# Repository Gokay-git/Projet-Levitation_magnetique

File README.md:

# Lévitation magnétique 2 axes — ENSEA

Un objet aimanté lévite au-dessus d'un plateau. Sa position latérale (X, Y), naturellement
instable, est mesurée par 3 capteurs à effet Hall et stabilisée en temps réel par 4 bobines
pilotées par une carte NUCLEO-L476RG.

**Objectif phase 1 : lévitation stable d'un objet d'au moins 800 g pour le 15 décembre 2026.**

**Carte de puissance** (shield enfiché sur la Nucleo) — [vue de dessous](Docs/images/puissance_dessous.png)

**Plateau de mesure** (3 capteurs à effet Hall) — [vue de dessous](Docs/images/plateau_dessous.png)

## Contenu du dépôt

| Dossier | Contenu |
|---|---|
| [`Hardware/`](Hardware) | Les 2 cartes KiCad : puissance et plateau |
| [`Firmware/`](Firmware) | Le projet STM32CubeIDE `LM_V2` (boucle de lévitation à 5 kHz) |
| [`Outils/`](Outils) | `lm_outil.py` : lecture du log série, calcul de L, ω₀ et β, courbes |
| [`Simulation/`](Simulation) | Le firmware compilé pour PC et testé sur un modèle de la maquette |
| [`Docs/`](Docs) | Schémas en PDF, rendus des cartes |

## Versions

Les versions figées sont dans les [Releases](../../releases) :

| Version | Contenu |
|---|---|
| `firmware-v2.0` | Projet STM32CubeIDE complet (zip) et outil PC |
| `pcb-v1.9.3` | Fichiers Gerber des 2 cartes, à envoyer au fabricant |

## État au 15 novembre 2026

- **Cartes V1.9.3** : vérification DRC sans erreur, prêtes à être commandées.
- **Firmware V2** : compile sans avertissement et a été validé en simulation (modèle instable
  2 axes + L293D + ADC, résultats dans [`Simulation/`](Simulation)). Il n'a pas encore été testé
  sur la maquette.
- **Valeurs provisoires** dans `Firmware/LM_V2/Core/Inc/LM_config.h` : R et L des bobines,
  ω₀ et β de chaque axe. Elles seront mesurées avec l'outil PC une fois les cartes reçues.

## Démarrer

- **Cartes** : schémas en PDF dans `Docs/schemas`, composants à commander dans les
  `nomenclature.csv` de `Hardware/`. Pour modifier : KiCad 7 ou plus récent, ouvrir
  `Hardware/LM_puissance/LM_puissance.kicad_pro` ou `Hardware/LM_plateau/LM_plateau.kicad_pro`.
- **Firmware** : STM32CubeIDE, **File → Open Projects from File System** → `Firmware/LM_V2`,
  puis **Project → Clean** et **Ctrl+B**. Mode d'emploi détaillé : `Firmware/LM_V2/LISEZMOI.txt`.
- **Outil PC** : voir [`Outils/README.md`](Outils/README.md).
- **Simulation** : `python Simulation/simuler.py` (compilateur C nécessaire), voir
  [`Simulation/README.md`](Simulation/README.md).

## Règles de travail

- Une seule branche `main`. Pour une modification risquée, créer une branche courte
  (ex. `pcb-v2`), puis la fusionner dans `main` par une pull request et la supprimer.
- Pas de zip ni de fichiers générés dans le dépôt : les versions figées vont dans les Releases.
- Les fichiers gardent toujours le même nom (pas de numéro de version dans le nom) :
  l'historique Git conserve toutes les versions.
- Une tâche = une *Issue*, assignée à un membre de l'équipe.

## Équipe

Gökay, Dylan, Subhen, Elias — ENSEA.

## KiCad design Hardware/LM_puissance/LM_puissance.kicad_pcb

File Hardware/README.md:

# Cartes électroniques (KiCad) — version V1.9.3

| Carte | Rôle | Composants principaux |
|---|---|---|
| `LM_puissance/` | Shield enfiché sur la NUCLEO-L476RG (CN7 / CN10) : commande des 4 bobines et acquisition | 2 × L293D (ponts X et Y), 4 × shunt 0,1 Ω 1 W + INA240A1, filtres RC des entrées ADC, régulateur L7805, protection d'entrée (P-MOS IRF4905, TVS SMBJ15A, fusible), bornier 12 V |
| `LM_plateau/` | Plateau de mesure de position, relié à la carte de puissance par un connecteur JST-XH | 3 × capteur à effet Hall DRV5055A4 (H1, H2, H3) |

Chaque dossier contient le projet (`.kicad_pro`), le schéma (`.kicad_sch`), le routage (`.kicad_pcb`)
et la **nomenclature** (`nomenclature.csv`, affichée sous forme de tableau par GitHub).
Les schémas sont aussi en PDF, lisibles sans KiCad, dans [`Docs/schemas`](../Docs/schemas).

## Composants à commander

| Carte | Nomenclature | Pièces |
|---|---|---|
| Puissance | [`LM_puissance/nomenclature.csv`](LM_puissance/nomenclature.csv) | 71 pièces (69 composants + 2 supports DIP-16) |
| Plateau | [`LM_plateau/nomenclature.csv`](LM_plateau/nomenclature.csv) | 7 composants |

À prévoir en plus, hors cartes :
- 1 carte NUCLEO-L476RG ;
- 1 câble JST-XH 6 points entre les deux cartes, câblé 1 vers 1 (2 boîtiers XHP-6 et 12 contacts, ou câble pré-serti) ;
- 1 alimentation 12 V continue (la carte est protégée par un fusible 2 A temporisé) ;
- 8 vis M3 et entretoises (4 trous de fixation par carte) ;
- les 4 bobines et les aimants (voir le point ouvert ci-dessous).

### Carte de puissance — dessus

### Carte de puissance — dessous (vue retournée)

### Plateau — dessus et dessous (vue retournée)

## Fabrication

Les fichiers Gerber de la version V1.9.3 sont dans la Release **`pcb-v1.9.3`** du dépôt.
Pour les régénérer après une modification : dans l'éditeur de PCB, **Fichiers → Fichiers de fabrication → Gerbers**.

## Points ouverts

- Les positions de H1, H2 et H3 sur le plateau sont provisoires.
- La partie physique n'est pas encore documentée : bobines (nombre de spires, fil, R, L), aimants
  (type, dimensions), objet en lévitation. Ce sont ces grandeurs qui fixent les valeurs de
  `Firmware/LM_V2/Core/Inc/LM_config.h`.
- Les valeurs de puissance (pistes, shunts) sont dimensionnées pour le L293D : à revoir en cas de passage à un pont MOSFET.

## Historique

| Version | Changement |
|---|---|
| V1.9.3 | Sérigraphie allégée : seuls restent les repères utiles au montage. Cuivre, vernis et perçages identiques à la V1.9.2 |
| V1.9.2 | Allègement des vias de masse, DRC sans erreur |

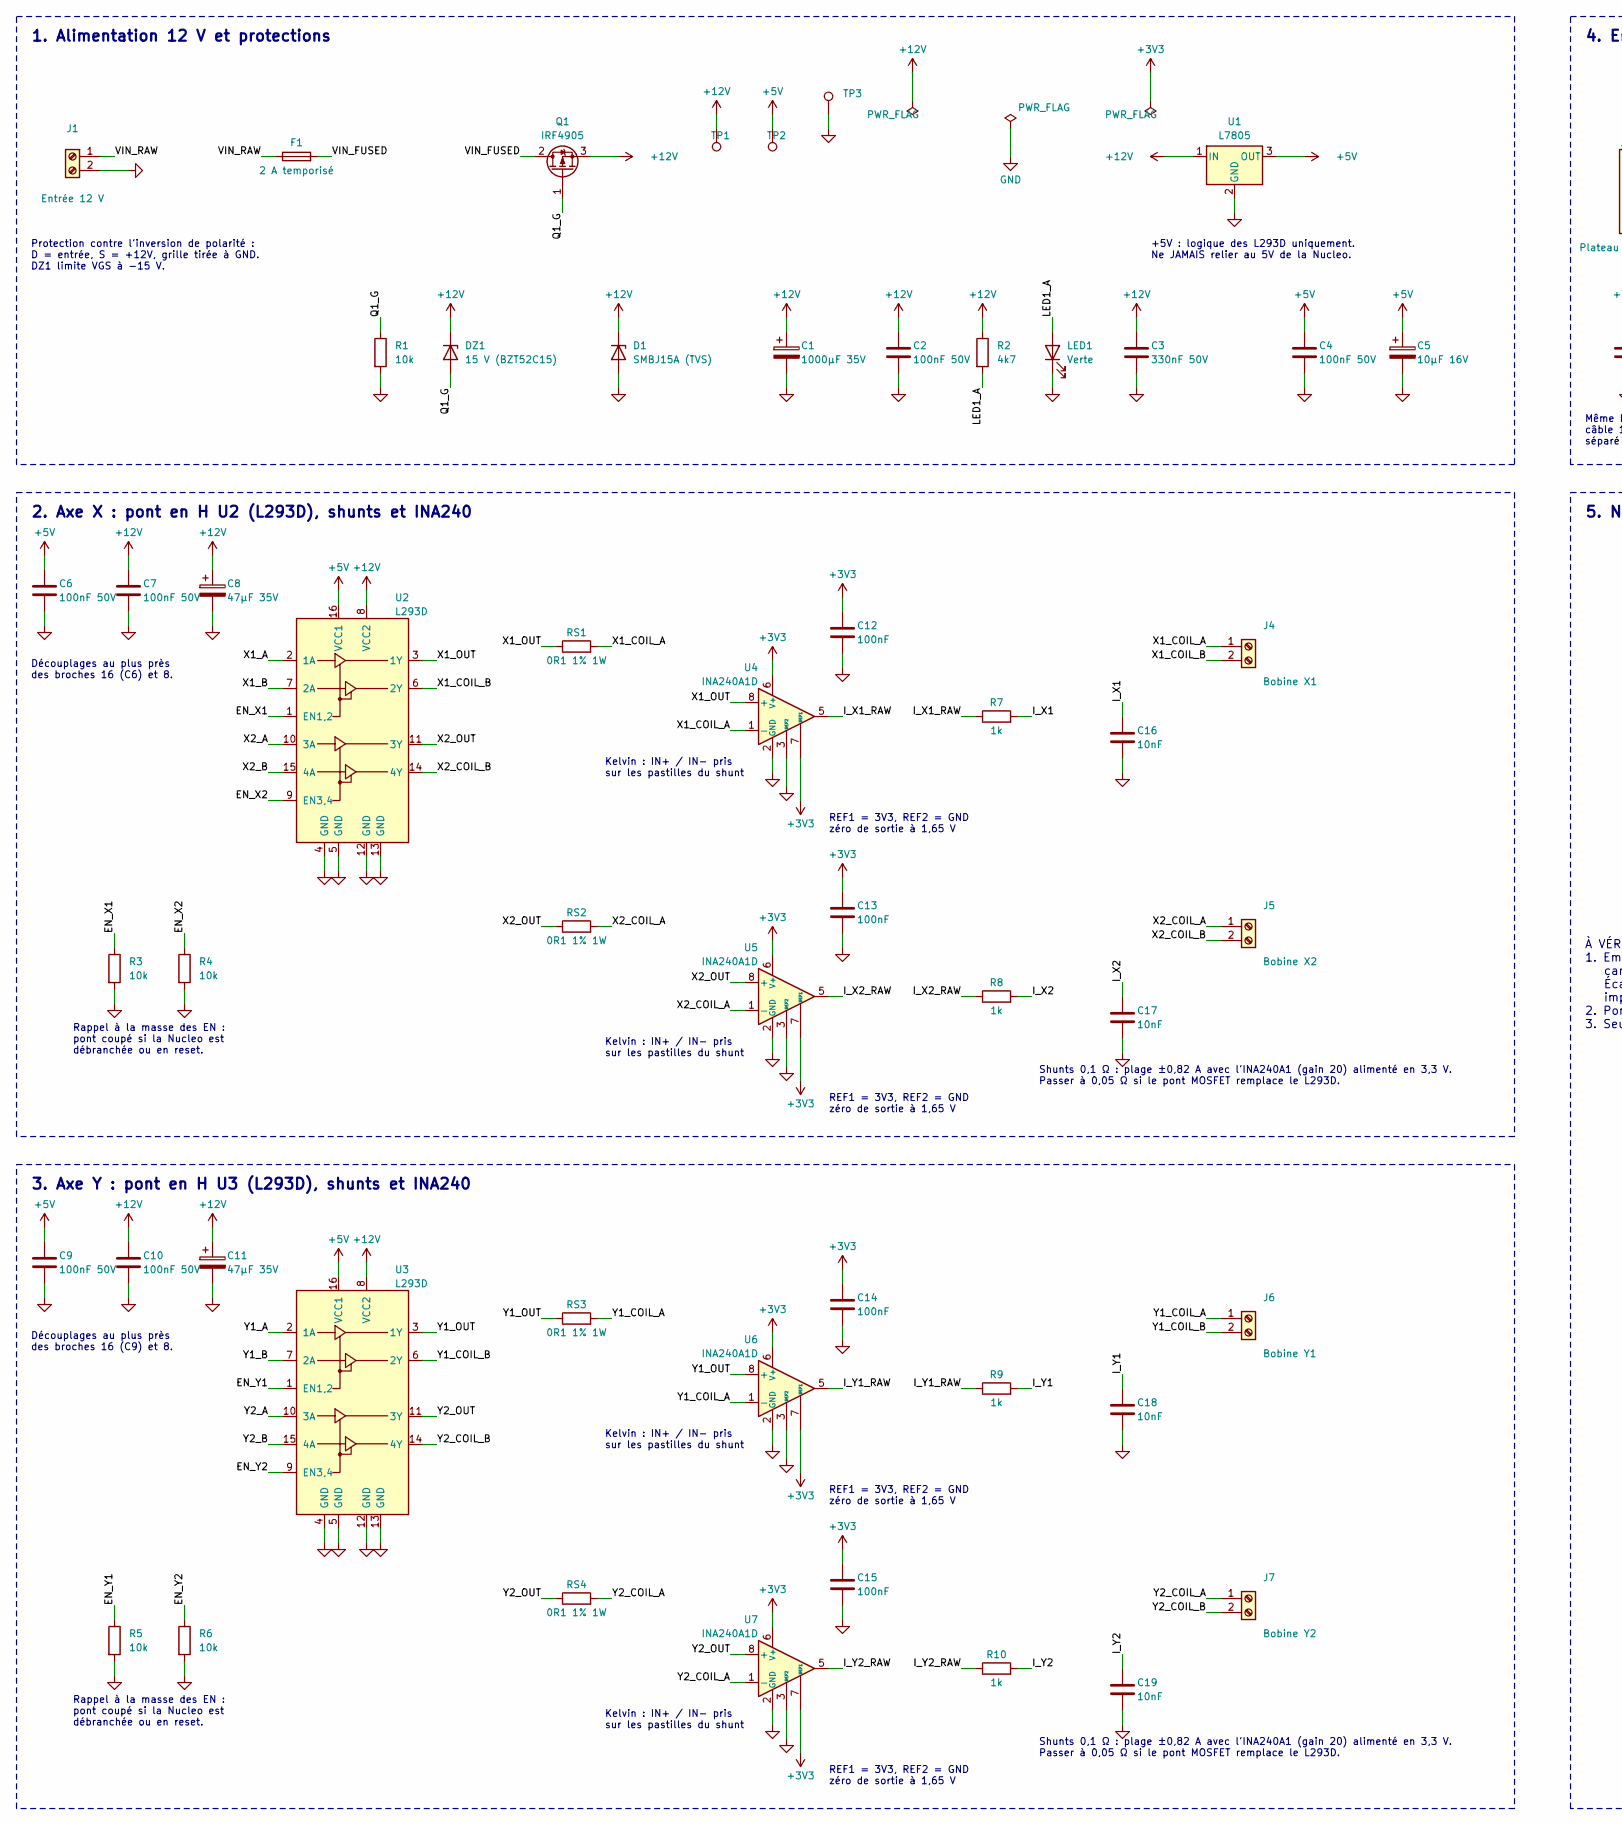
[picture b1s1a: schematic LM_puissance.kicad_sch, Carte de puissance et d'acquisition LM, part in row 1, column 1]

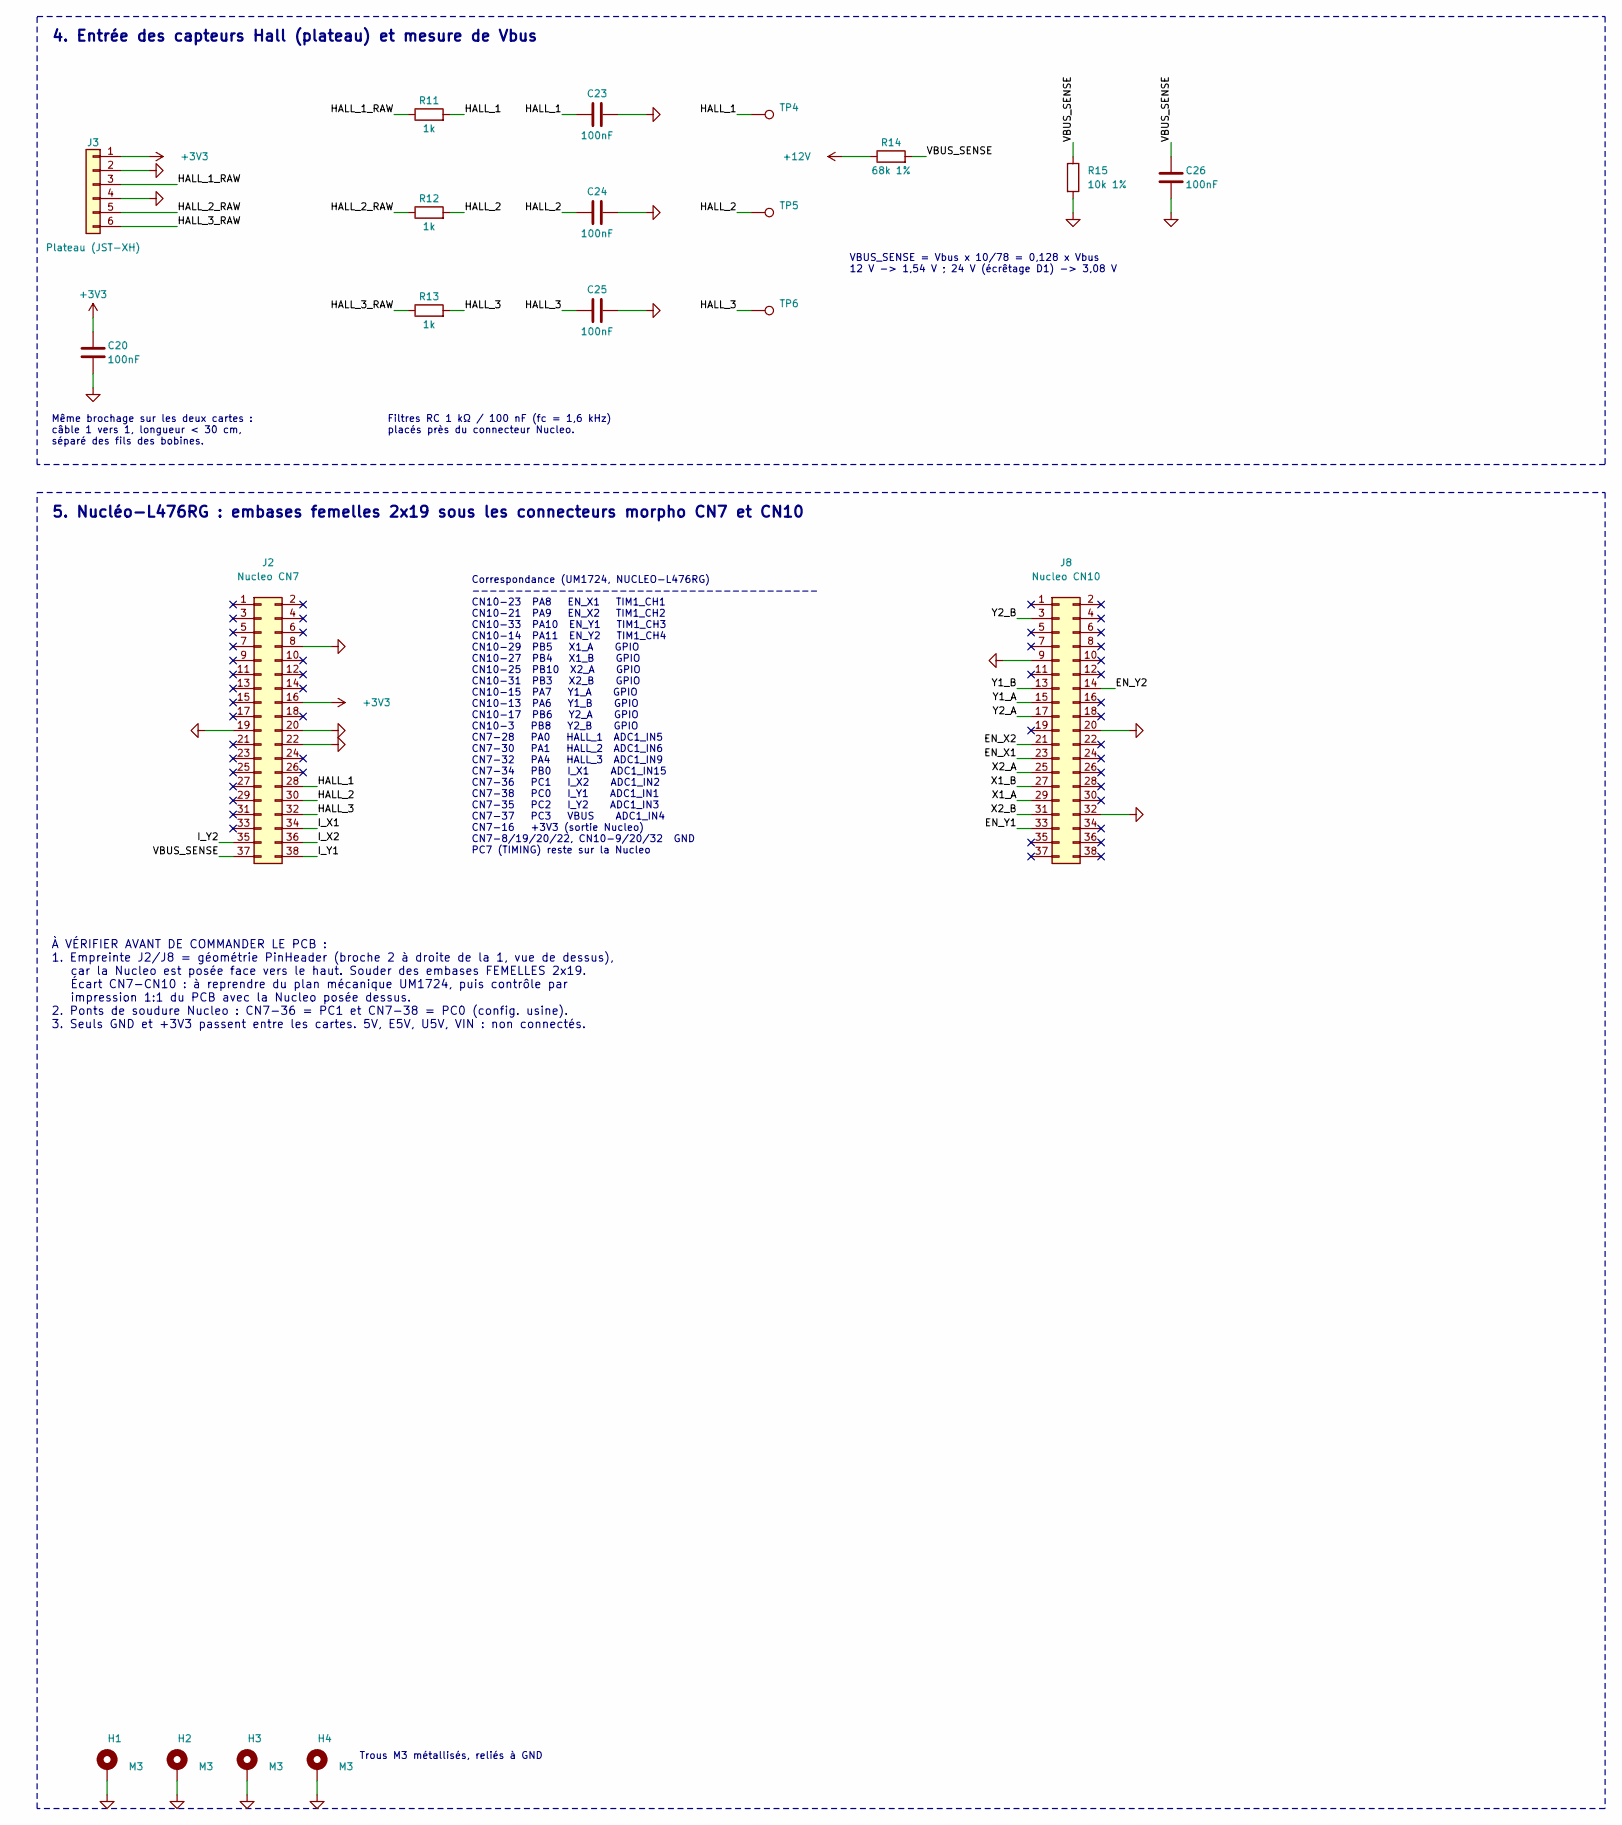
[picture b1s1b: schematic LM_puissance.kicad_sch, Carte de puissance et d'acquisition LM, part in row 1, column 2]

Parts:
C1: 1000µF 35V; CP_Radial_D10.0mm_P5.00mm
C2, C4, C6, C7, C9, C10: 100nF 50V; C_0805_2012Metric_Pad1.18x1.45mm_HandSolder
C3: 330nF 50V; C_0805_2012Metric_Pad1.18x1.45mm_HandSolder
C5: 10µF 16V; CP_Radial_D5.0mm_P2.00mm
C8, C11: 47µF 35V; CP_Radial_D6.3mm_P2.50mm
C12, C13, C14, C15, C20, C23, C24, C25, C26: 100nF; C_0805_2012Metric_Pad1.18x1.45mm_HandSolder
C16, C17, C18, C19: 10nF; C_0805_2012Metric_Pad1.18x1.45mm_HandSolder
D1: SMBJ15A (TVS); D_SMB
DZ1: 15 V (BZT52C15); D_SOD-123
F1: 2 A temporisé; Fuseholder_Cylinder-5x20mm_Schurter_0031_8201_Horizontal_Op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
H1, H2, H3, H4: M3; MountingHole_3.2mm_M3_Pad_Via
J1: Entrée 12 V; TerminalBlock_Phoenix_MKDS-1,5-2-5.08_1x02_P5.08mm_Horizont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
J2: Nucleo CN7; PinHeader_2x19_P2.54mm_Vertical
J3: Plateau (JST-XH); JST_XH_S6B-XH-A_1x06_P2.50mm_Horizontal
J4: Bobine X1; TerminalBlock_Phoenix_MKDS-1,5-2-5.08_1x02_P5.08mm_Horizont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
J5: Bobine X2; TerminalBlock_Phoenix_MKDS-1,5-2-5.08_1x02_P5.08mm_Horizont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
J6: Bobine Y1; TerminalBlock_Phoenix_MKDS-1,5-2-5.08_1x02_P5.08mm_Horizont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
J7: Bobine Y2; TerminalBlock_Phoenix_MKDS-1,5-2-5.08_1x02_P5.08mm_Horizont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
J8: Nucleo CN10; PinHeader_2x19_P2.54mm_Vertical
LED1: Verte; LED_0805_2012Metric_Pad1.15x1.40mm_HandSolder
Q1: IRF4905; TO-220-3_Vertical
R1, R3, R4, R5, R6: 10k; R_0805_2012Metric_Pad1.20x1.40mm_HandSolder
R2: 4k7; R_0805_2012Metric_Pad1.20x1.40mm_HandSolder
R7, R8, R9, R10, R11, R12, R13: 1k; R_0805_2012Metric_Pad1.20x1.40mm_HandSolder
R14: 68k 1%; R_0805_2012Metric_Pad1.20x1.40mm_HandSolder
R15: 10k 1%; R_0805_2012Metric_Pad1.20x1.40mm_HandSolder
RS1, RS2, RS3, RS4: 0R1 1% 1W; R_2512_6332Metric
TP1: +12V; TestPoint_Loop_D2.50mm_Drill1.0mm
TP2: +5V; TestPoint_Loop_D2.50mm_Drill1.0mm
TP3: GND; TestPoint_Loop_D2.50mm_Drill1.0mm
TP4: HALL_1; TestPoint_Loop_D2.50mm_Drill1.0mm
TP5: HALL_2; TestPoint_Loop_D2.50mm_Drill1.0mm
TP6: HALL_3; TestPoint_Loop_D2.50mm_Drill1.0mm
U1: L7805; TO-220-3_Vertical
U2, U3: L293D; DIP-16_W7.62mm_Socket
U4, U5, U6, U7: INA240A1D; SOIC-8_3.9x4.9mm_P1.27mm

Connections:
+3V3: C12.1, C13.1, C14.1, C15.1, C20.1, J2.16, J3.1, U4.6 (V+), U4.7 (REF1), U5.6 (V+), U5.7 (REF1), U6.6 (V+), U6.7 (REF1), U7.6 (V+), U7.7 (REF1)
+5V: C4.1, C5.1, C6.1, C9.1, TP2.1, U1.3 (OUT), U2.16 (VCC1), U3.16 (VCC1)
+12V: C1.1, C2.1, C3.1, C7.1, C8.1, C10.1, C11.1, D1.1 (K), DZ1.1 (K), Q1.3 (S), R2.1, R14.1, TP1.1, U1.1 (IN), U2.8 (VCC2), U3.8 (VCC2)
/EN_X1: J8.23, R3.1, U2.1 (EN1,2)
/EN_X2: J8.21, R4.1, U2.9 (EN3,4)
/EN_Y1: J8.33, R5.1, U3.1 (EN1,2)
/EN_Y2: J8.14, R6.1, U3.9 (EN3,4)
/HALL_1: C23.1, J2.28, R11.2, TP4.1
/HALL_1_RAW: J3.3, R11.1
/HALL_2: C24.1, J2.30, R12.2, TP5.1
/HALL_2_RAW: J3.5, R12.1
/HALL_3: C25.1, J2.32, R13.2, TP6.1
/HALL_3_RAW: J3.6, R13.1
/I_X1: C16.1, J2.34, R7.2
/I_X1_RAW: R7.1, U4.5
/I_X2: C17.1, J2.36, R8.2
/I_X2_RAW: R8.1, U5.5
/I_Y1: C18.1, J2.38, R9.2
/I_Y1_RAW: R9.1, U6.5
/I_Y2: C19.1, J2.35, R10.2
/I_Y2_RAW: R10.1, U7.5
/LED1_A: LED1.2 (A), R2.2
/Q1_G: DZ1.2 (A), Q1.1 (G), R1.1
/VBUS_SENSE: C26.1, J2.37, R14.2, R15.1
/VIN_FUSED: F1.2, Q1.2 (D)
/VIN_RAW: F1.1, J1.1
/X1_A: J8.29, U2.2 (1A)
/X1_B: J8.27, U2.7 (2A)
/X1_COIL_A: J4.1, RS1.2, U4.1 (-)
/X1_COIL_B: J4.2, U2.6 (2Y)
/X1_OUT: RS1.1, U2.3 (1Y), U4.8 (+)
/X2_A: J8.25, U2.10 (3A)
/X2_B: J8.31, U2.15 (4A)
/X2_COIL_A: J5.1, RS2.2, U5.1 (-)
/X2_COIL_B: J5.2, U2.14 (4Y)
/X2_OUT: RS2.1, U2.11 (3Y), U5.8 (+)
/Y1_A: J8.15, U3.2 (1A)
/Y1_B: J8.13, U3.7 (2A)
/Y1_COIL_A: J6.1, RS3.2, U6.1 (-)
/Y1_COIL_B: J6.2, U3.6 (2Y)
/Y1_OUT: RS3.1, U3.3 (1Y), U6.8 (+)
/Y2_A: J8.17, U3.10 (3A)
/Y2_B: J8.3, U3.15 (4A)
/Y2_COIL_A: J7.1, RS4.2, U7.1 (-)
/Y2_COIL_B: J7.2, U3.14 (4Y)
/Y2_OUT: RS4.1, U3.11 (3Y), U7.8 (+)
GND: C1.2, C2.2, C3.2, C4.2, C5.2, C6.2, C7.2, C8.2, C9.2, C10.2, C11.2, C12.2, C13.2, C14.2, C15.2, C16.2, C17.2, C18.2, C19.2, C20.2, C23.2, C24.2, C25.2, C26.2, D1.2 (A), H1.1, H2.1, H3.1, H4.1, J1.2, J2.8, J2.19, J2.20, J2.22, J3.2, J3.4, J8.9, J8.20, J8.32, LED1.1 (K), R1.2, R3.2, R4.2, R5.2, R6.2, R15.2, TP3.1, U1.2 (GND), U2.4 (GND), U2.5 (GND), U2.12 (GND), U2.13 (GND), U3.4 (GND), U3.5 (GND), U3.12 (GND), U3.13 (GND), U4.2 (GND), U4.3 (REF2), U4.4 (GND), U5.2 (GND), U5.3 (REF2), U5.4 (GND), U6.2 (GND), U6.3 (REF2), U6.4 (GND), U7.2 (GND), U7.3 (REF2), U7.4 (GND)

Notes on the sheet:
1. Alimentation 12 V et protections
Protection contre l'inversion de polarité : D = entrée, S = +12V, grille tirée à GND. DZ1 limite VGS à -15 V.
+5V : logique des L293D uniquement. Ne JAMAIS relier au 5V de la Nucleo.
2. Axe X : pont en H U2 (L293D), shunts et INA240
Rappel à la masse des EN : pont coupé si la Nucleo est débranchée ou en reset.
Découplages au plus près des broches 16 (C6) et 8.
Kelvin : IN+ / IN- pris sur les pastilles du shunt
REF1 = 3V3, REF2 = GND zéro de sortie à 1,65 V
Shunts 0,1 Ω : plage ±0,82 A avec l'INA240A1 (gain 20) alimenté en 3,3 V. Passer à 0,05 Ω si le pont MOSFET remplace le L293D.
3. Axe Y : pont en H U3 (L293D), shunts et INA240
Découplages au plus près des broches 16 (C9) et 8.
4. Entrée des capteurs Hall (plateau) et mesure de Vbus
Même brochage sur les deux cartes : câble 1 vers 1, longueur < 30 cm, séparé des fils des bobines.
Filtres RC 1 kΩ / 100 nF (fc = 1,6 kHz) placés près du connecteur Nucleo.
VBUS_SENSE = Vbus x 10/78 = 0,128 x Vbus 12 V -> 1,54 V ; 24 V (écrêtage D1) -> 3,08 V
5. Nucléo-L476RG : embases femelles 2x19 sous les connecteurs morpho CN7 et CN10
Correspondance (UM1724, NUCLEO-L476RG) ---------------------------------------- CN10-23 PA8 EN_X1 TIM1_CH1 CN10-21 PA9 EN_X2 TIM1_CH2 CN10-33 PA10 EN_Y1 TIM1_CH3 CN10-14 PA11 EN_Y2 TIM1_CH4 CN10-29 PB5 X1_A GPIO CN10-27 PB4 X1_B GPIO CN10-25 PB10 X2_A GPIO CN10-31 PB3 X2_B GPIO CN10-15 PA7 Y1_A GPI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
À VÉRIFIER AVANT DE COMMANDER LE PCB : 1. Empreinte J2/J8 = géométrie PinHeader (broche 2 à droite de la 1, vue de dessus), car la Nucleo est posée face vers le haut. Souder des embases FEMELLES 2x19. Écart CN7-CN10 : à reprendre du plan mécanique UM1724, puis contrôle par impression 1:1 du PCB ave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
Trous M3 métallisés, reliés à GND

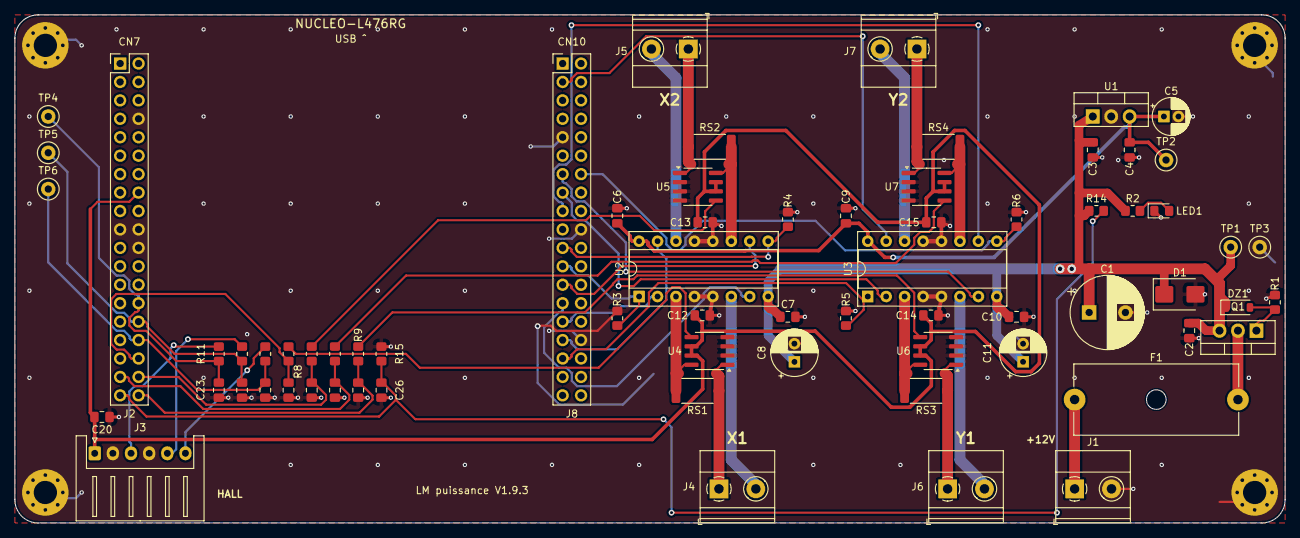
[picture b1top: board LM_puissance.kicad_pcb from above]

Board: 2 copper layers, 175.0 x 70.0 mm, 73 parts (0 on the bottom side), 47 nets.

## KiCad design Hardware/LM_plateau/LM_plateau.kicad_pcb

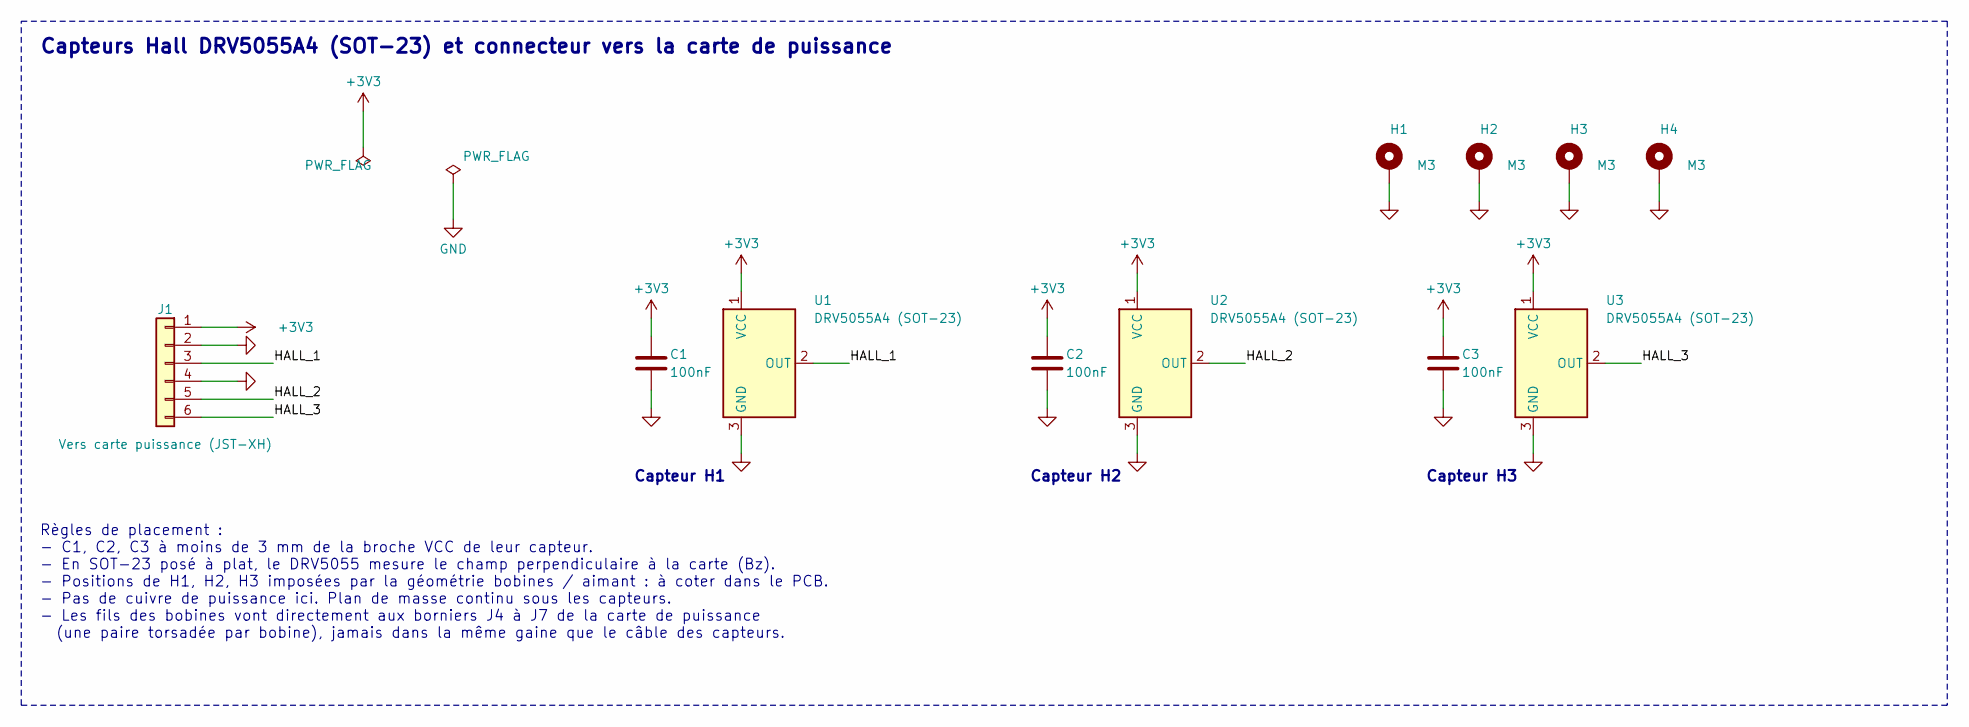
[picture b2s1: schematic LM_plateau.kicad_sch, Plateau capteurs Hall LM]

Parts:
C1, C2, C3: 100nF; C_0805_2012Metric_Pad1.18x1.45mm_HandSolder
H1, H2, H3, H4: M3; MountingHole_3.2mm_M3_Pad_Via
J1: Vers carte puissance (JST-XH); JST_XH_S6B-XH-A_1x06_P2.50mm_Horizontal
U1, U2, U3: DRV5055A4 (SOT-23); SOT-23

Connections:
+3V3: C1.1, C2.1, C3.1, J1.1, U1.1 (VCC), U2.1 (VCC), U3.1 (VCC)
/HALL_1: J1.3, U1.2 (OUT)
/HALL_2: J1.5, U2.2 (OUT)
/HALL_3: J1.6, U3.2 (OUT)
GND: C1.2, C2.2, C3.2, H1.1, H2.1, H3.1, H4.1, J1.2, J1.4, U1.3 (GND), U2.3 (GND), U3.3 (GND)

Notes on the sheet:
Capteurs Hall DRV5055A4 (SOT-23) et connecteur vers la carte de puissance
Capteur H1
Capteur H2
Capteur H3
Règles de placement : - C1, C2, C3 à moins de 3 mm de la broche VCC de leur capteur. - En SOT-23 posé à plat, le DRV5055 mesure le champ perpendiculaire à la carte (Bz). - Positions de H1, H2, H3 imposées par la géométrie bobines / aimant : à coter dans le PCB. - Pas de cuivre de puissance ici. Pla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

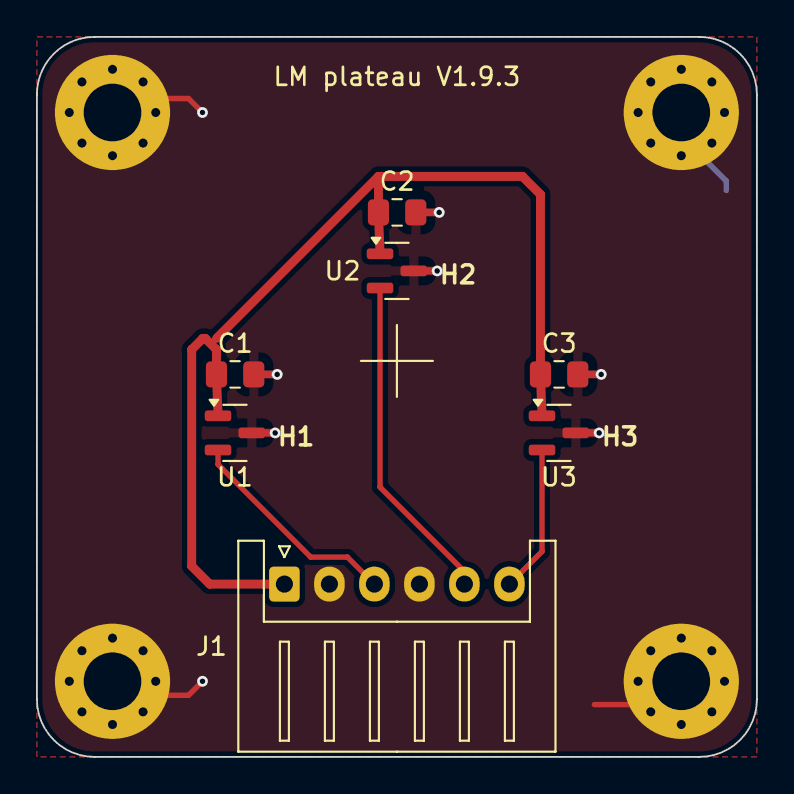
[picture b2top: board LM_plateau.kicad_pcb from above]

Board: 2 copper layers, 40.0 x 40.0 mm, 11 parts (0 on the bottom side), 5 nets.

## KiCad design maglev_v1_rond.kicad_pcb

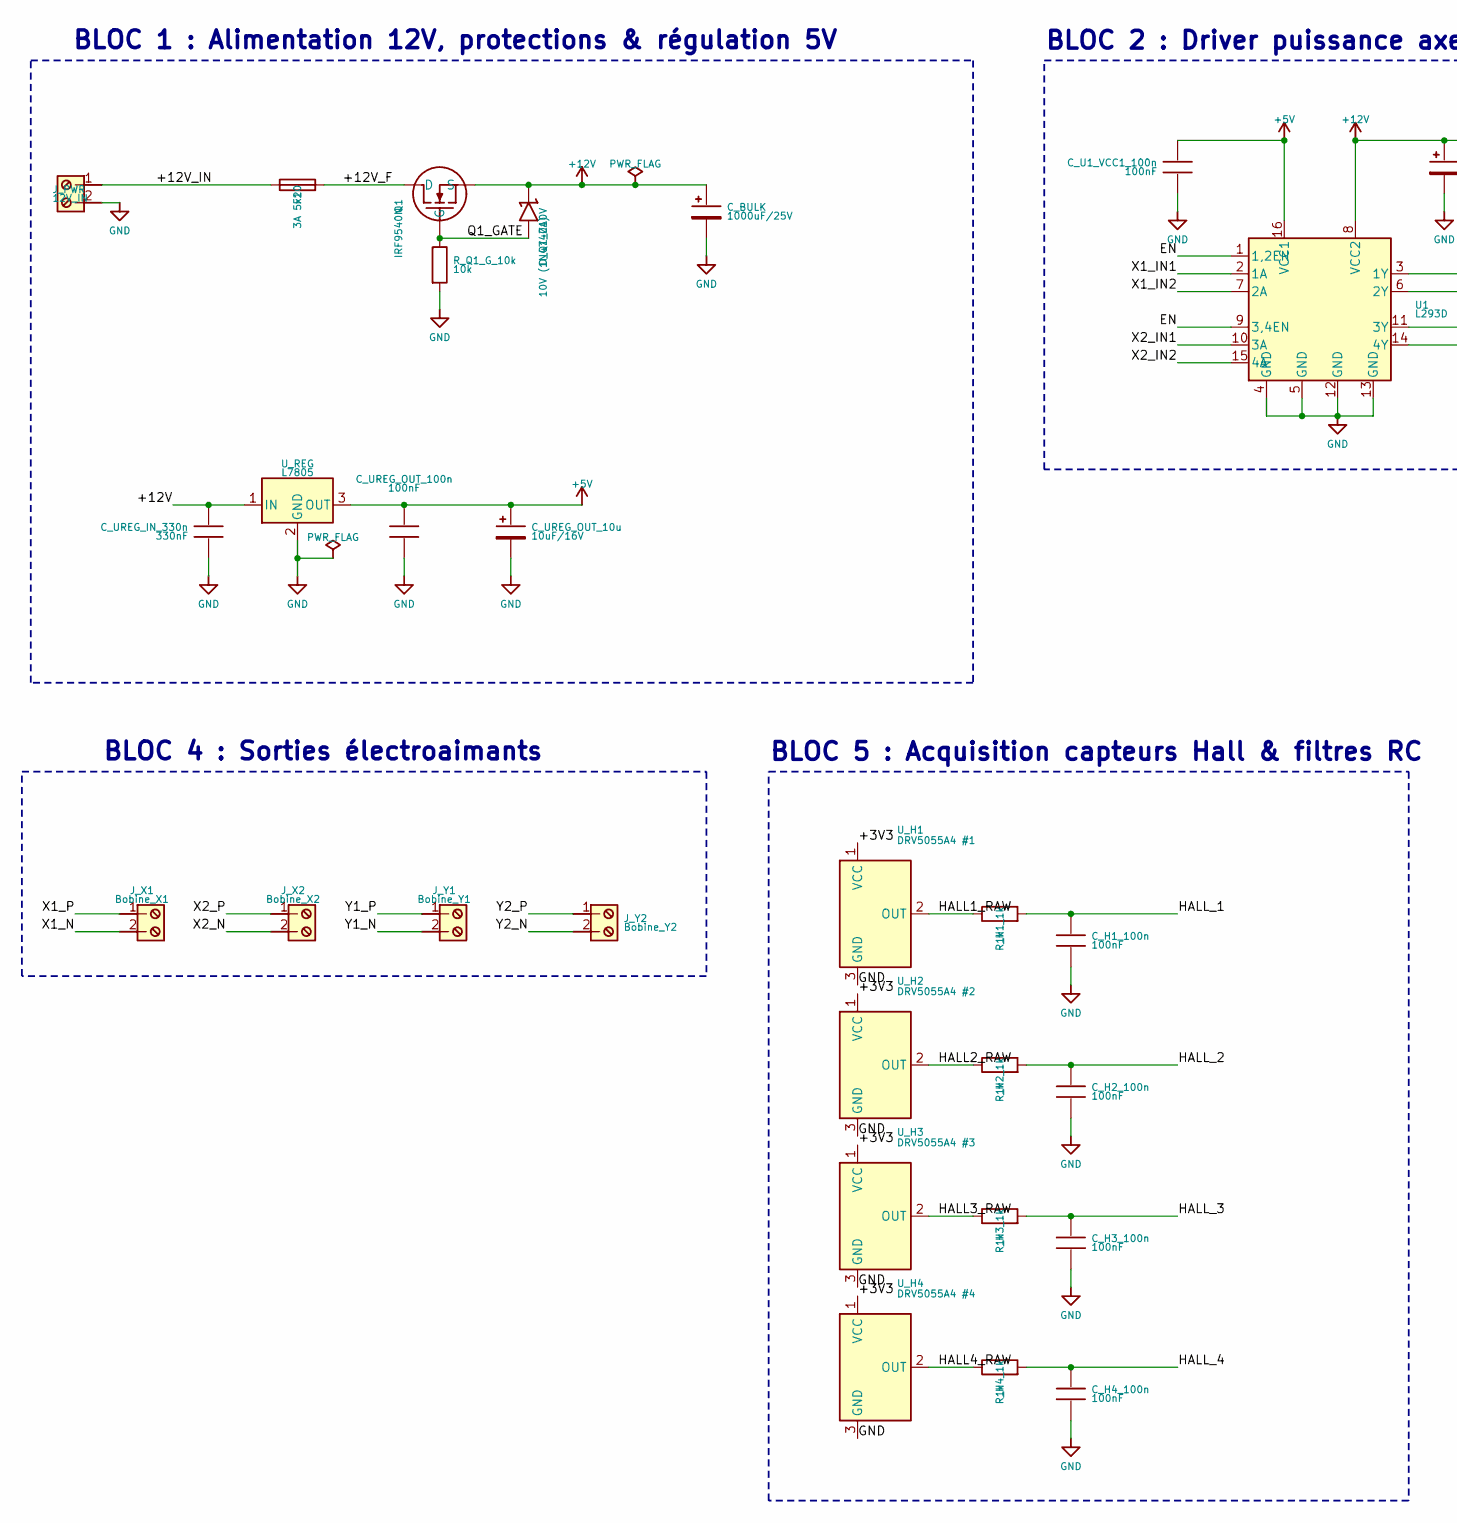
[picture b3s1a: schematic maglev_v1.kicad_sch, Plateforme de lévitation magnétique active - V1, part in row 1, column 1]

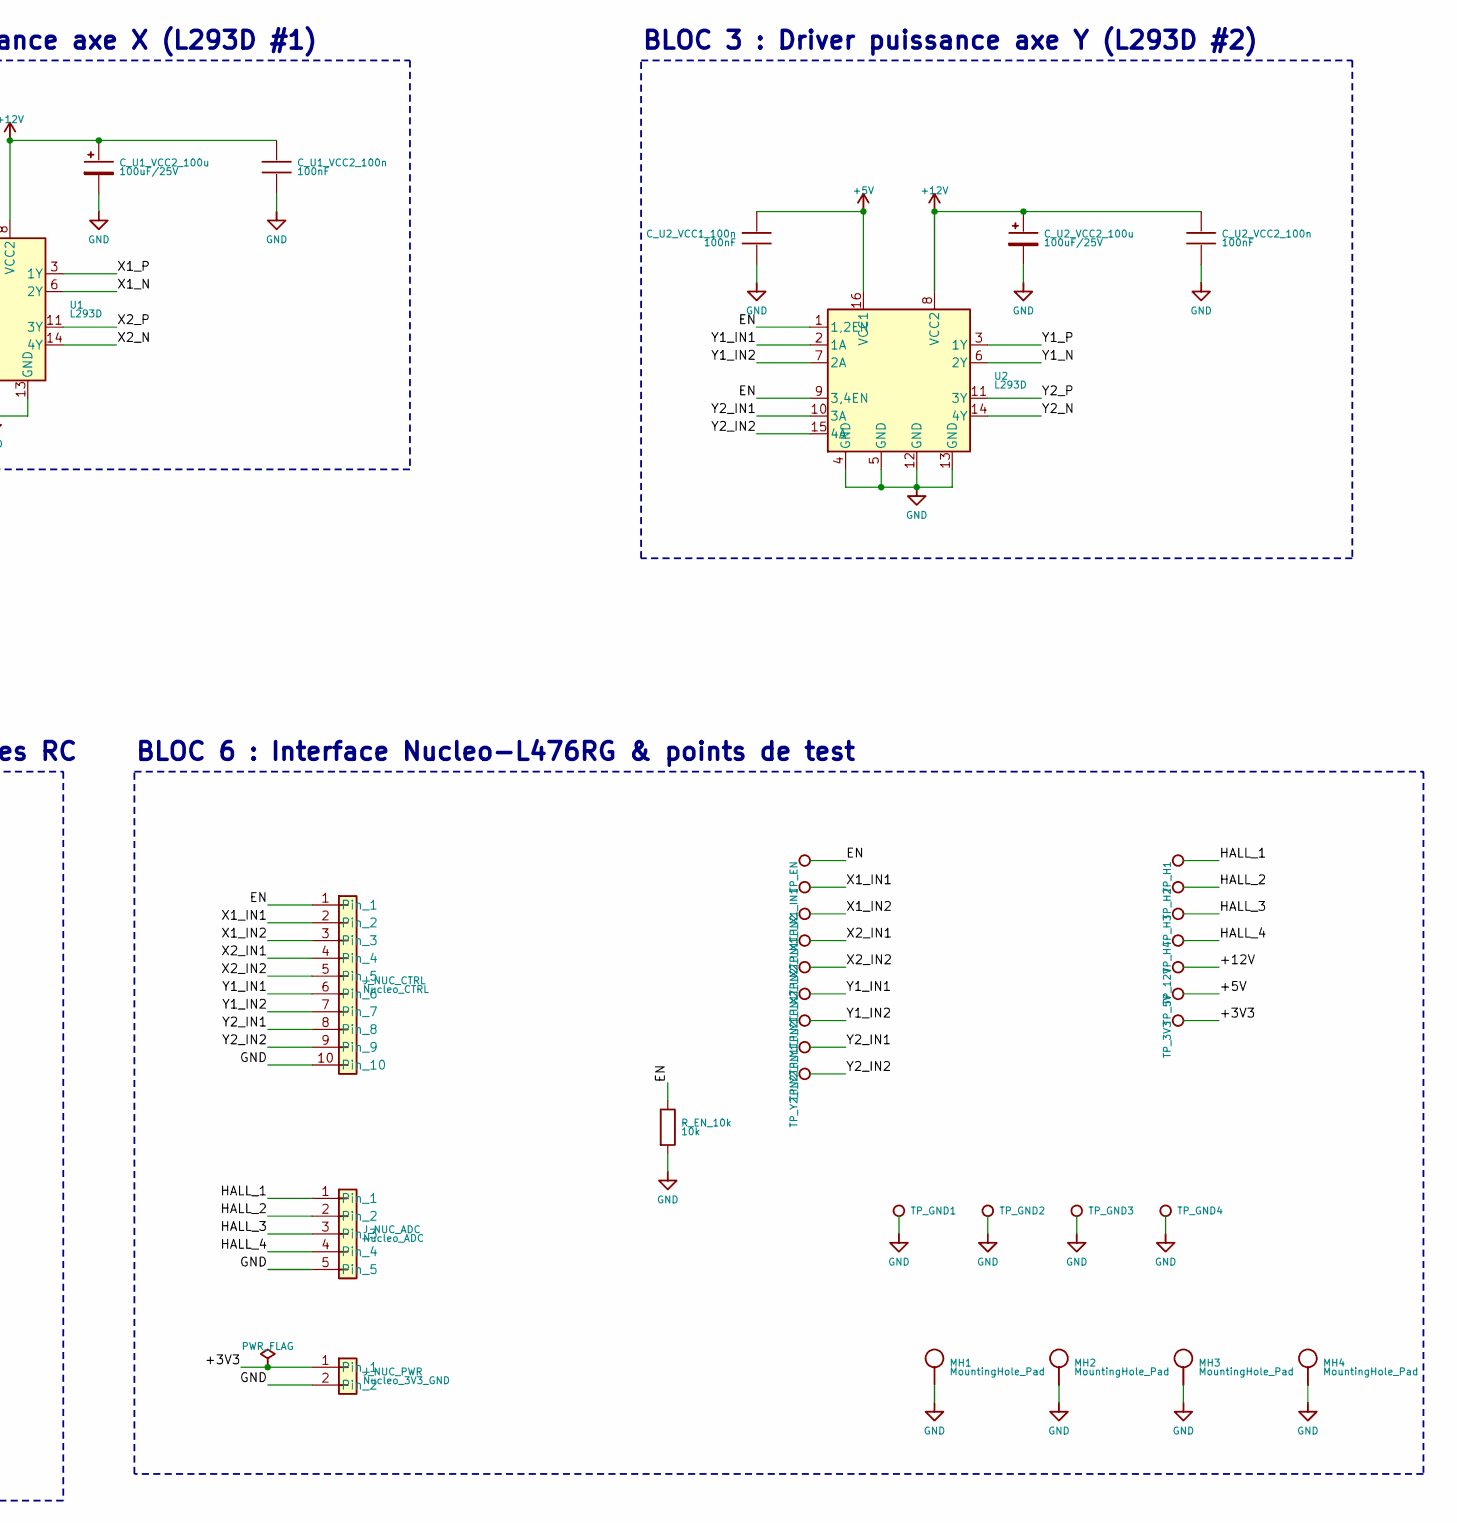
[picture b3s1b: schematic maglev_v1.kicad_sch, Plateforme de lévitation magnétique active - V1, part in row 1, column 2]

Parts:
C_BULK: 1000uF/25V; CP_Radial_D10.0mm_P5.00mm
C_H1_100n, C_H2_100n, C_H3_100n, C_H4_100n: 100nF; C_0805_2012Metric_Pad1.18x1.45mm_HandSolder
C_U1_VCC1_100n, C_U1_VCC2_100n, C_U2_VCC1_100n, C_U2_VCC2_100n: 100nF; C_0805_2012Metric_Pad1.18x1.45mm_HandSolder
C_U1_VCC2_100u, C_U2_VCC2_100u: 100uF/25V; CP_Radial_D6.3mm_P2.50mm
C_UREG_IN_330n: 330nF; C_0805_2012Metric_Pad1.18x1.45mm_HandSolder
C_UREG_OUT_10u: 10uF/16V; CP_Radial_D5.0mm_P2.00mm
C_UREG_OUT_100n: 100nF; C_0805_2012Metric_Pad1.18x1.45mm_HandSolder
D_Q1_Z10V: 10V (1N4740A); D_DO-41_SOD81_P10.16mm_Horizontal
F1: 3A 5x20; Fuseholder_Cylinder-5x20mm_P22.50mm_Custom
J_NUC_ADC: Nucleo_ADC; PinHeader_1x05_P2.54mm_Vertical
J_NUC_CTRL: Nucleo_CTRL; PinHeader_1x10_P2.54mm_Vertical
J_NUC_PWR: Nucleo_3V3_GND; PinHeader_1x02_P2.54mm_Vertical
J_PWR: 12V_IN; TerminalBlock_Phoenix_MKDS-1,5-2-5.08_1x02_P5.08mm_Horizont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
J_X1: Bobine_X1; TerminalBlock_Phoenix_MKDS-1,5-2-5.08_1x02_P5.08mm_Horizont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
J_X2: Bobine_X2; TerminalBlock_Phoenix_MKDS-1,5-2-5.08_1x02_P5.08mm_Horizont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
J_Y1: Bobine_Y1; TerminalBlock_Phoenix_MKDS-1,5-2-5.08_1x02_P5.08mm_Horizont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
J_Y2: Bobine_Y2; TerminalBlock_Phoenix_MKDS-1,5-2-5.08_1x02_P5.08mm_Horizont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
MH1, MH2, MH3, MH4: MountingHole_Pad; MountingHole_3.2mm_M3_DIN965_Pad
Q1: IRF9540N; TO-220-3_Vertical
R_EN_10k: 10k; R_0805_2012Metric_Pad1.20x1.40mm_HandSolder
R_H1_1k, R_H2_1k, R_H3_1k, R_H4_1k: 1k; R_0805_2012Metric_Pad1.20x1.40mm_HandSolder
R_Q1_G_10k: 10k; R_0805_2012Metric_Pad1.20x1.40mm_HandSolder
TP_3V3: TP_3V3; TestPoint_Pad_D2.0mm
TP_5V: TP_5V; TestPoint_Pad_D2.0mm
TP_12V: TP_12V; TestPoint_Pad_D2.0mm
TP_EN: TP_EN; TestPoint_Pad_D2.0mm
TP_GND1: TP_GND1; TestPoint_Pad_D2.0mm
TP_GND2: TP_GND2; TestPoint_Pad_D2.0mm
TP_GND3: TP_GND3; TestPoint_Pad_D2.0mm
TP_GND4: TP_GND4; TestPoint_Pad_D2.0mm
TP_H1: TP_H1; TestPoint_Pad_D2.0mm
TP_H2: TP_H2; TestPoint_Pad_D2.0mm
TP_H3: TP_H3; TestPoint_Pad_D2.0mm
TP_H4: TP_H4; TestPoint_Pad_D2.0mm
TP_X1_IN1: TP_X1_IN1; TestPoint_Pad_D2.0mm
TP_X1_IN2: TP_X1_IN2; TestPoint_Pad_D2.0mm
TP_X2_IN1: TP_X2_IN1; TestPoint_Pad_D2.0mm
TP_X2_IN2: TP_X2_IN2; TestPoint_Pad_D2.0mm
TP_Y1_IN1: TP_Y1_IN1; TestPoint_Pad_D2.0mm
TP_Y1_IN2: TP_Y1_IN2; TestPoint_Pad_D2.0mm
TP_Y2_IN1: TP_Y2_IN1; TestPoint_Pad_D2.0mm
TP_Y2_IN2: TP_Y2_IN2; TestPoint_Pad_D2.0mm
U1, U2: L293D; DIP-16_W7.62mm_Socket
U_H1: DRV5055A4 #1; SOT-23
U_H2: DRV5055A4 #2; SOT-23
U_H3: DRV5055A4 #3; SOT-23
U_H4: DRV5055A4 #4; SOT-23
U_REG: L7805; TO-220-3_Vertical

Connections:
+3V3: J_NUC_PWR.1, TP_3V3.1, U_H1.1 (VCC), U_H2.1 (VCC), U_H3.1 (VCC), U_H4.1 (VCC)
+5V: C_U1_VCC1_100n.1, C_U2_VCC1_100n.1, C_UREG_OUT_10u.1, C_UREG_OUT_100n.1, TP_5V.1, U1.16 (VCC1), U2.16 (VCC1), U_REG.3 (OUT)
+12V: C_BULK.1, C_U1_VCC2_100n.1, C_U1_VCC2_100u.1, C_U2_VCC2_100n.1, C_U2_VCC2_100u.1, C_UREG_IN_330n.1, D_Q1_Z10V.1 (K), Q1.3 (S), TP_12V.1, U1.8 (VCC2), U2.8 (VCC2), U_REG.1 (IN)
+12V_F: F1.2, Q1.2 (D)
+12V_IN: F1.1, J_PWR.1
EN: J_NUC_CTRL.1, R_EN_10k.1, TP_EN.1, U1.1 (1,2EN), U1.9 (3,4EN), U2.1 (1,2EN), U2.9 (3,4EN)
GND: C_BULK.2, C_H1_100n.2, C_H2_100n.2, C_H3_100n.2, C_H4_100n.2, C_U1_VCC1_100n.2, C_U1_VCC2_100n.2, C_U1_VCC2_100u.2, C_U2_VCC1_100n.2, C_U2_VCC2_100n.2, C_U2_VCC2_100u.2, C_UREG_IN_330n.2, C_UREG_OUT_10u.2, C_UREG_OUT_100n.2, J_NUC_ADC.5, J_NUC_CTRL.10, J_NUC_PWR.2, J_PWR.2, MH1.1, MH2.1, MH3.1, MH4.1, R_EN_10k.2, R_Q1_G_10k.2, TP_GND1.1, TP_GND2.1, TP_GND3.1, TP_GND4.1, U1.4 (GND), U1.5 (GND), U1.12 (GND), U1.13 (GND), U2.4 (GND), U2.5 (GND), U2.12 (GND), U2.13 (GND), U_H1.3 (GND), U_H2.3 (GND), U_H3.3 (GND), U_H4.3 (GND), U_REG.2 (GND)
HALL1_RAW: R_H1_1k.1, U_H1.2 (OUT)
HALL2_RAW: R_H2_1k.1, U_H2.2 (OUT)
HALL3_RAW: R_H3_1k.1, U_H3.2 (OUT)
HALL4_RAW: R_H4_1k.1, U_H4.2 (OUT)
HALL_1: C_H1_100n.1, J_NUC_ADC.1, R_H1_1k.2, TP_H1.1
HALL_2: C_H2_100n.1, J_NUC_ADC.2, R_H2_1k.2, TP_H2.1
HALL_3: C_H3_100n.1, J_NUC_ADC.3, R_H3_1k.2, TP_H3.1
HALL_4: C_H4_100n.1, J_NUC_ADC.4, R_H4_1k.2, TP_H4.1
Q1_GATE: D_Q1_Z10V.2 (A), Q1.1 (G), R_Q1_G_10k.1
X1_IN1: J_NUC_CTRL.2, TP_X1_IN1.1, U1.2 (1A)
X1_IN2: J_NUC_CTRL.3, TP_X1_IN2.1, U1.7 (2A)
X1_N: J_X1.2, U1.6 (2Y)
X1_P: J_X1.1, U1.3 (1Y)
X2_IN1: J_NUC_CTRL.4, TP_X2_IN1.1, U1.10 (3A)
X2_IN2: J_NUC_CTRL.5, TP_X2_IN2.1, U1.15 (4A)
X2_N: J_X2.2, U1.14 (4Y)
X2_P: J_X2.1, U1.11 (3Y)
Y1_IN1: J_NUC_CTRL.6, TP_Y1_IN1.1, U2.2 (1A)
Y1_IN2: J_NUC_CTRL.7, TP_Y1_IN2.1, U2.7 (2A)
Y1_N: J_Y1.2, U2.6 (2Y)
Y1_P: J_Y1.1, U2.3 (1Y)
Y2_IN1: J_NUC_CTRL.8, TP_Y2_IN1.1, U2.10 (3A)
Y2_IN2: J_NUC_CTRL.9, TP_Y2_IN2.1, U2.15 (4A)
Y2_N: J_Y2.2, U2.14 (4Y)
Y2_P: J_Y2.1, U2.11 (3Y)

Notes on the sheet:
BLOC 6 : Interface Nucleo-L476RG & points de test
BLOC 1 : Alimentation 12V, protections & régulation 5V
BLOC 2 : Driver puissance axe X (L293D #1)
BLOC 3 : Driver puissance axe Y (L293D #2)
BLOC 4 : Sorties électroaimants
BLOC 5 : Acquisition capteurs Hall & filtres RC

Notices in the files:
Firmware/LM_V2/Core/Src/main.c:
Copyright (c) 2026 STMicroelectronics.
All rights reserved.
This software is licensed under terms that can be found in the LICENSE file
